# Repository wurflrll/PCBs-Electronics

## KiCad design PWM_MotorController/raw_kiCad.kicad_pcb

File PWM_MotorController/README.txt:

Controls the power provided to a DC motor through PWM control.  There are two
halves to the circuit, the digital half records the speed-setting and allows 
the user to increment it, the other half is the analog circuit that allows a 
digital input to modify pulse width.  This means no microcontroller is used
and a single digital oscillator can provide a number of different pulse 
widths (also some fine-tuning is possible through resistor values).

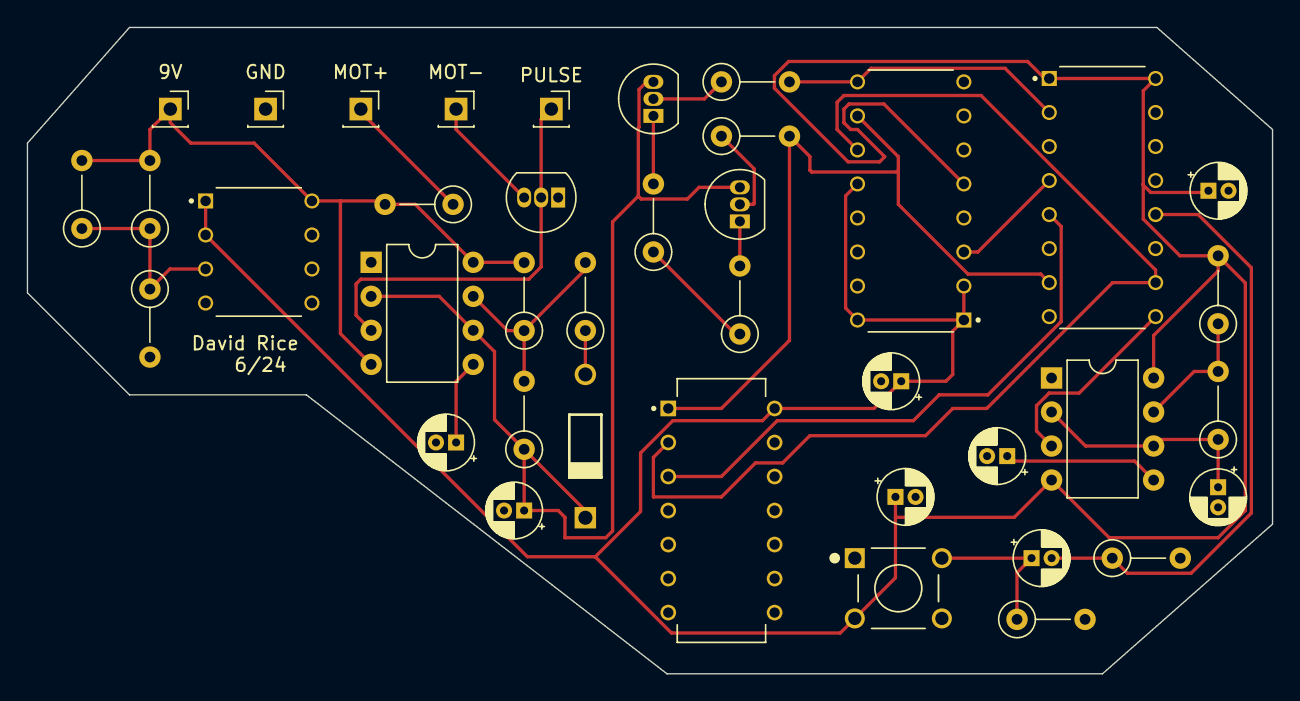
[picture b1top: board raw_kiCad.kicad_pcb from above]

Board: 2 copper layers, 93.0 x 48.3 mm, 39 parts (0 on the bottom side), 26 nets.

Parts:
9V: TestPoint; PinSocket_1x01_P2.54mm_Vertical
C1, C2, C3, C4, C5, C6, C7, C8: C_Polarized_US; CP_Radial_D4.0mm_P1.50mm
D1: IN4007; DIOAD1070W78L470D235P
GND: TestPoint; PinSocket_1x01_P2.54mm_Vertical
MOT+: TestPoint; PinSocket_1x01_P2.54mm_Vertical
MOT-: TestPoint; PinSocket_1x01_P2.54mm_Vertical
Q1, Q2: 2N3904; TO-92_Inline
Q3: 2N7000; TO-92_Inline
R1, R2, R3, R4, R5, R6, R7, R8, R9, R10, R11, R12, R13, R14, R15: R; R_Axial_DIN0207_L6.3mm_D2.5mm_P5.08mm_Vertical
S1: FSM8JH; SW_FSM8JH
TP5: TestPoint; PinSocket_1x01_P2.54mm_Vertical
U1, U5: SA555P; DIP-8_W7.62mm
U2: CD40175BE; DIP794W45P254L1969H508Q16
U3: CD4070BEE4; DIP794W45P254L1969H508Q14
U4: CD4051BEE4; DIP794W45P254L1969H508Q16
U6: LM358PE3; DIP794W45P254L959H508Q8

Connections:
+5V: C6.1, C7.1, C8.1, R1.2, S1.2, U1.4 (R), U1.8 (VCC), U2.1 (~CLR), U2.16 (VDD), U3.14 (VDD), U4.1 (CH4_IN/OUT), U4.2 (CH6_IN/OUT), U4.5 (CH5_IN/OUT), U4.12 (CH3_IN/OUT), U4.16 (VDD), U6.1 (1OUT), U6.2 (1IN-)
+9V: 9V.1, R5.2, R12.2, R13.2, R14.2, U5.4 (R), U5.8 (VCC), U6.8 (VCC)
GND: C1.2, C2.2, C4.2, C5.2, C6.2, C7.2, C8.2, GND.1, Q3.1 (S), R3.2, R4.2, R7.1, R8.1, R15.2, U1.1 (GND), U2.8 (VSS), U3.7 (VSS), U4.4 (CH7_IN/OUT), U4.6 (INH), U4.7 (VEE), U4.8 (VSS), U4.13 (CH0_IN/OUT), U4.14 (CH1_IN/OUT), U4.15 (CH2_IN/OUT), U5.1 (GND), U6.4 (GND)
unnamed: C3.1, R4.1, S1.3
unnamed: D1.A, R11.1
unnamed: Q1.2 (B), R9.1
unnamed: C5.1, D1.C, Q1.3 (C), Q2.3 (C), R6.1, U5.2 (TR), U5.6 (THR)
unnamed: Q1.1 (E), R7.2
unnamed: Q2.2 (B), R10.1
unnamed: Q2.1 (E), R8.2
unnamed: MOT-.1, Q3.3 (D)
unnamed: Q3.2 (G), TP5.1, U5.3 (Q)
unnamed: MOT+.1, R12.1
unnamed: C1.1, U1.5 (CV)
unnamed: R1.1, R2.2, U1.7 (DIS)
unnamed: U1.3 (Q), U2.9 (CLK)
unnamed: C2.1, R2.1, U1.2 (TR), U1.6 (THR)
unnamed: U2.4 (D1), U4.3 (COM_OUT/IN)
unnamed: U2.5 (D2), U3.3 (J)
unnamed: C3.2, R3.1, U2.12 (D3)
unnamed: R9.2, U2.2 (Q1), U4.9 (C)
unnamed: R10.2, U2.7 (Q2), U3.1 (A), U4.10 (B)
unnamed: U2.10 (Q3), U3.2 (B), U4.11 (A)
unnamed: C4.1, U5.5 (CV)
unnamed: R5.1, R6.2, R11.2, U5.7 (DIS)
unnamed: R13.1, R14.1, R15.1, U6.3 (1IN+)

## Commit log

2024-08-18 Adding some files
